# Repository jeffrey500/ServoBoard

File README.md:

# ServoBoard V2.1

## Introduction
This project contains a 2 layer PCB that has the designed purpose of driving up to 4 PWM servo motors of variable input voltage, with the entire board itself being powered by a variable voltage.  
This board is controlled by an atmega328PB and has 6n137 optocouplers.

## Microcontroller
The microcontroller (MCU) on this board is the atmega328PB which can be programmed via the USB-C connection on the side of the board through the use of a CH340C USB-to-UART serial converter IC.  
The atmega328PB was chosen as it is a simple and stable MCU that can be programmed using the Arduino IDE, and is an upgrade over the atmega328.
The MCU utilizes an external 16 MHz crystal oscillator. 

Note: the USB connection can only be used after initial bootloader burning (see ISP section).

## Power
There are 3 different voltages present on the board: input, servo, and 5V. 

Using the LM2596S buck voltage regulator, the board can utilize a maximum of 3A at the output of the Buck regulator. 
The efficiency of the LM2596S 92%. The board accepts a voltage range of 40V and can step it down to 1.25V-35V.
You can adjust the output voltage of the LM2596S by adjusting the screw on the blue potentiometer.
The potentiometer acts as a voltage divider which alters the internal PWM duty cycle. 

The use of an AMS1117-5.0 fixed 5V low dropout linear voltage regulator further steps down the voltage from the servo voltage to 5V to power the MCU.
The dropout range is 1.3V with a max input voltage of 15V.

Note: you should be careful when adjusting output of the LM2596S when using voltages higher than 15V as you can potentially destroy the AMS1117 LDO.
Additionally, the servo voltage should be high enough such that the MCU after the LDO has sufficient a sufficient voltage.

## Servo PWM pins
Servo motors can be driven using one or many of the 4 sets of SIGNAL-POWER-GROUND male header pins. 
The connected servo motors are driven by the voltage output of the LM2596S Buck Converter. 
A large 2200uF capacitor is placed very close to the servo pin headers to provide power during momentary high current draw. 

## Optocouplers
The Board contains 3 6n137 high-speed digital Optocouplers, mounted on DIP-8 sockets, allowing for interfacing with optical isolation.
The 6n137 mounted on the U5 DIP-8 socket is oriented as an input for digital signals while U4 and U6 are oriented as outputs.

## Board Design
This Board utilizes a 2 layer stackup. The top layer is signal with a ground pour.
The bottom layer is a ground plane of which effort was put in to ensure as much continuity as possible. 
The top and bottom ground layers are connected via stitching.
A power plane and cut is placed around the servo pin headers so that surges of power are drawn from the nearby capacitor.
Extra thermal vias are placed around the ground pin of the LM2596S.

## In-System Programming (ISP)
Following the assembly of the board you will need to do burn the bootloader of the board to be able to use the USB-C port to program the atmega328PB. 
To do this, it is recommended to use any Arduino in addition to its ability to be an [ISP flasher](https://docs.arduino.cc/built-in-examples/arduino-isp/ArduinoISP/).

### Schematic

### Board Without Pours

### Top Copper

### Bottom Copper

## Application
The design application of this board is within a CNC White board plotter //add link for which this board controls a pen plotter that is controlled by an Ardunio CNC Shield, interfacing through an optocoupler.
The board input voltage is 12V, with the servo needing 7V.

## BOM
The cost of each board at low production quantities is around $15 CAD.

## LICENSE
[ServoBoard](https://github.com/jeffrey500/ServoBoard) © 2026 by [Jeffrey Zhu](https://jzhu.ca) is licensed under [CC BY-NC 4.0](https://creativecommons.org/licenses/by-nc/4.0/)

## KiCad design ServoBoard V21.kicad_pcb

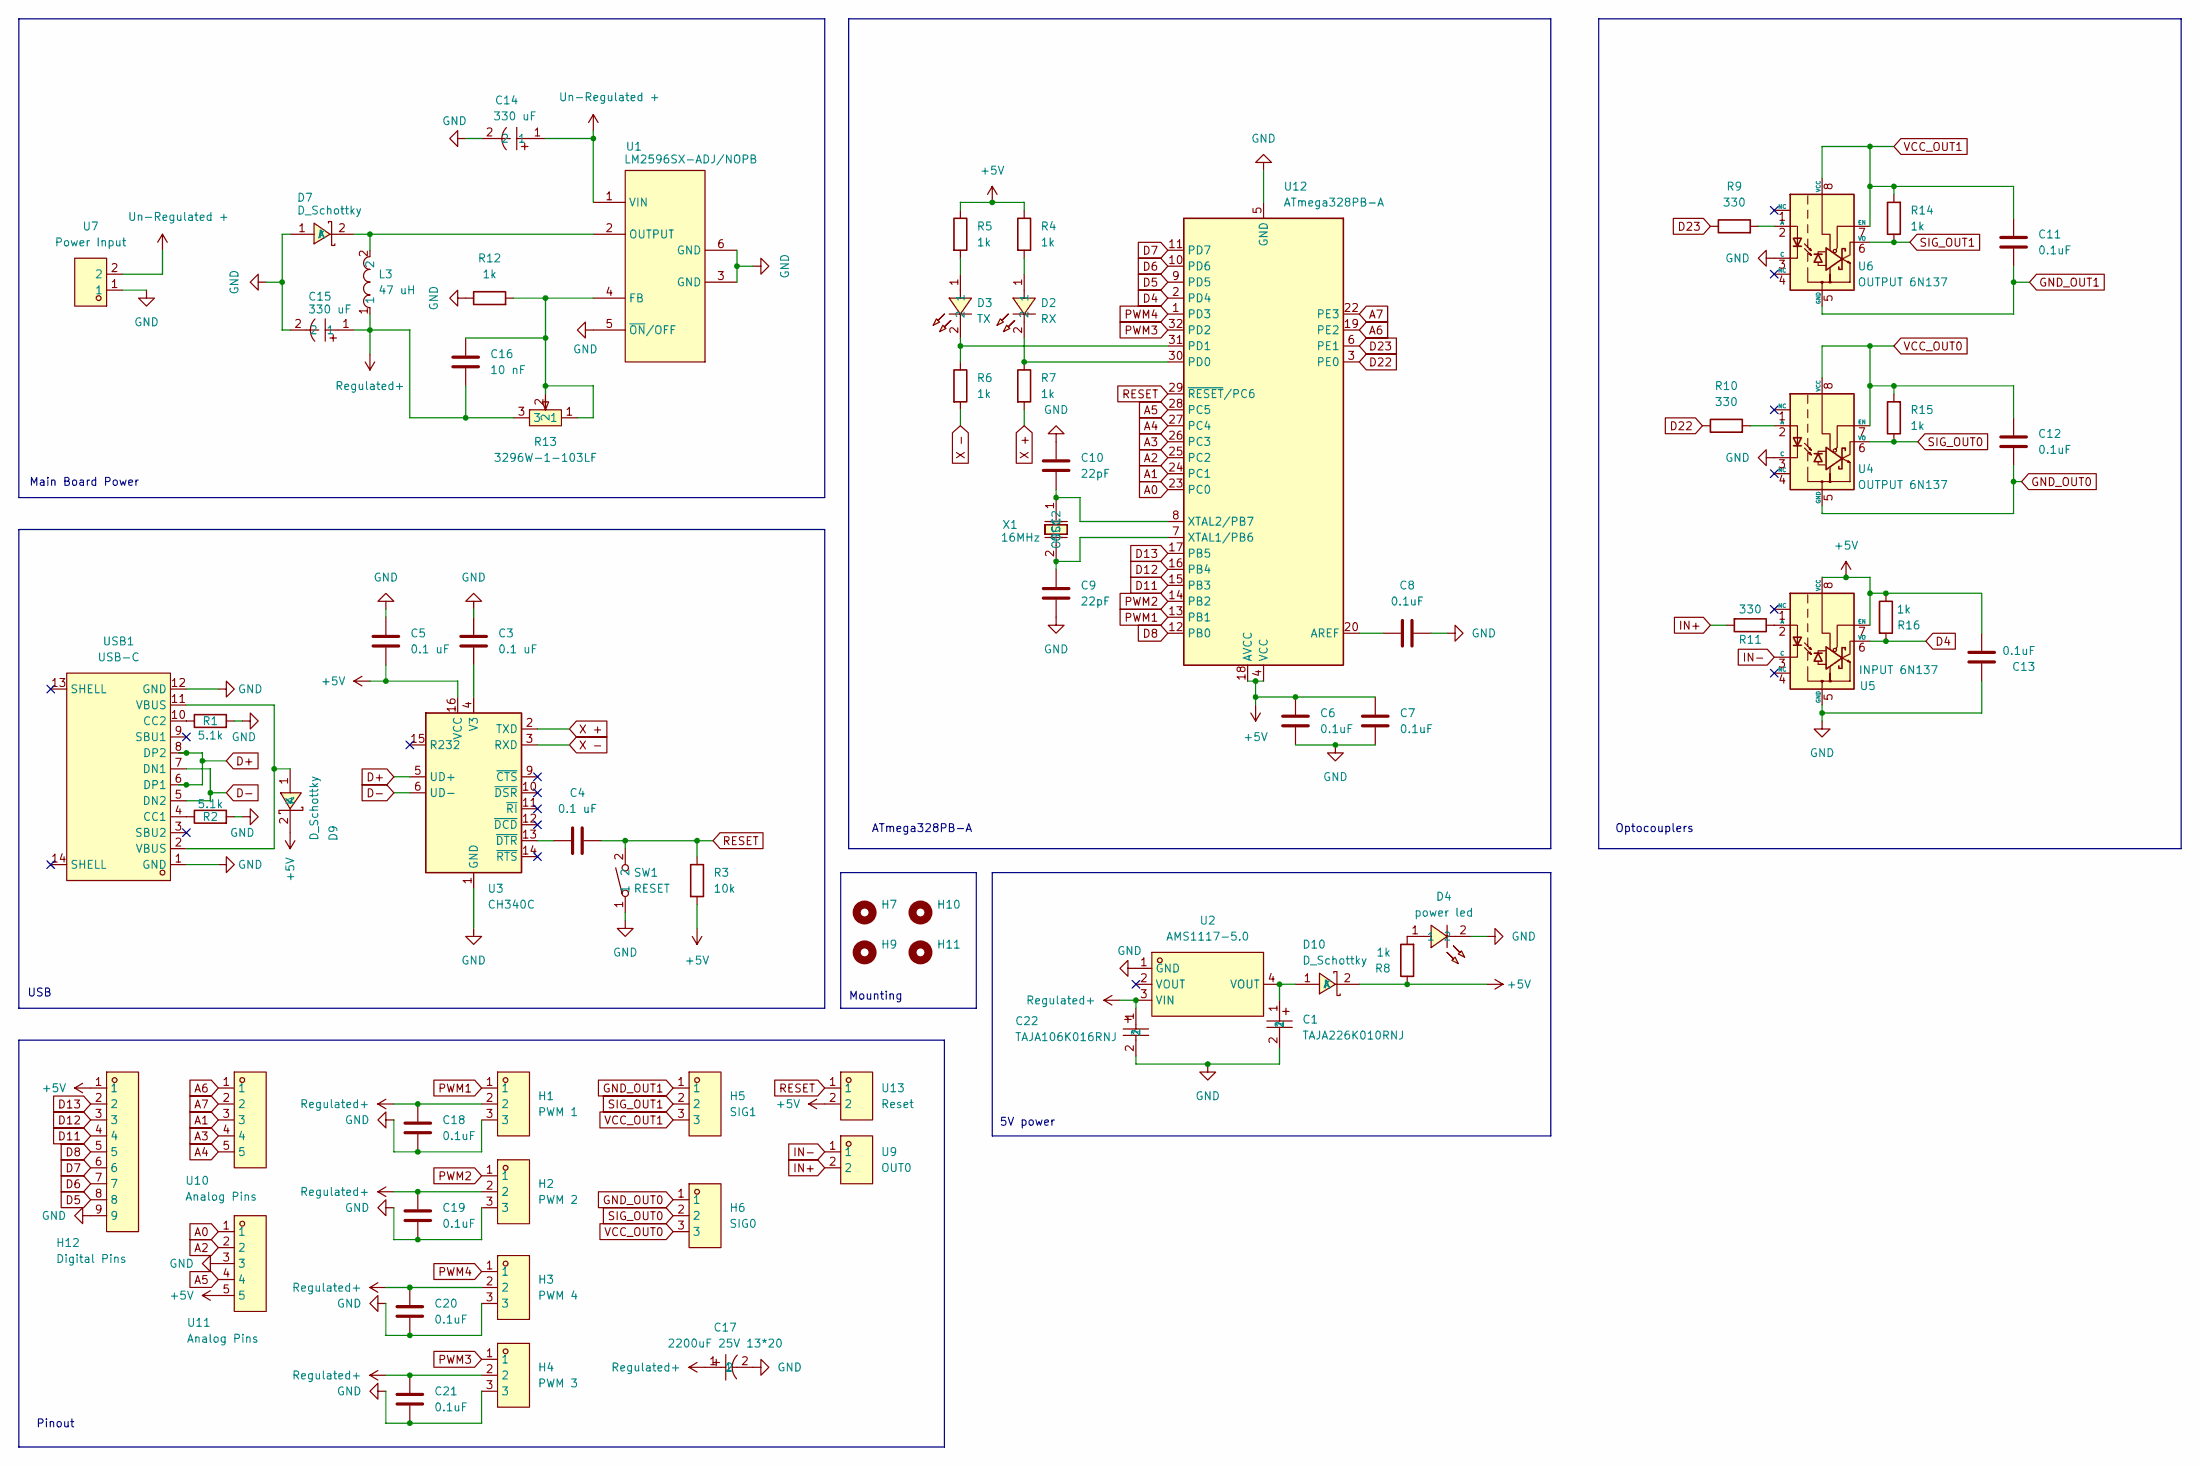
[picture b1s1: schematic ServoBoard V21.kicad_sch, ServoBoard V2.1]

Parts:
C1: TAJA226K010RNJ; CASE-A_3216; MPN TAJA226K010RNJ; LCSC Part C11366
C3, C4, C5: 0.1 uF; C_0805_2012Metric
C6, C7, C8, C11, C12, C13, C18, C19, C20, C21: 0.1uF; C_0805_2012Metric
C9, C10: 22pF; C_0805_2012Metric
C14, C15: 330 uF; CAP-TH_BD12.5-P5.00-D0.6-FD; LCSC Part C2835679
C16: 10 nF; C_0805_2012Metric
C17: 2200uF 25V 13*20; CAP-TH_BD13.0-P5.00-D1.2-FD; MPN KM228M025J20RR0VH2FP0; LCSC Part C44598
C22: TAJA106K016RNJ; CAP-SMD_L3.2-W1.6-RD-C7171; MPN TAJA106K016RNJ; LCSC Part C7171
D2: RX; LED1206-FD; LCSC Part C28310439
D3: TX; LED1206-FD; LCSC Part C28310439
D4: power led; LED1206-FD; LCSC Part C28310439
D7, D9, D10: D_Schottky; SMA_L4.4-W2.8-LS5.4-R-RD; LCSC Part C22452
H1: PWM 1; CONN-TH_HX-PZ2.54-1X3P-ZZ; LCSC Part C32713269
H2: PWM 2; CONN-TH_HX-PZ2.54-1X3P-ZZ; LCSC Part C32713269
H3: PWM 4; CONN-TH_HX-PZ2.54-1X3P-ZZ; LCSC Part C32713269
H4: PWM 3; CONN-TH_HX-PZ2.54-1X3P-ZZ; LCSC Part C32713269
H5: SIG1; CONN-TH_HX-PZ2.54-1X3P-ZZ; LCSC Part C32713269
H6: SIG0; CONN-TH_HX-PZ2.54-1X3P-ZZ; LCSC Part C32713269
H7, H9, H10, H11: MountingHole; MountingHole_4.3mm_M4
H12: Digital Pins; HDR-TH_9P-P2.54-V-F-3; LCSC Part C42372501
L3: 47 uH; IND-SMD_L12.3-W12.3; LCSC Part C962356
R1, R2: 5.1k; R_0805_2012Metric
R3: 10k; R_0805_2012Metric
R4, R5, R6, R7, R8, R12, R14, R15, R16: 1k; R_0805_2012Metric
R9, R10, R11: 330; R_0805_2012Metric
R13: 3296W-1-103LF; RES-ADJ-TH_3296W; MPN 3296W-1-103LF; LCSC Part C34846
SW1: RESET; SW-SMD_L4.0-W2.9-LS5.0; LCSC Part C557591
U1: LM2596SX-ADJ/NOPB; TO-263-5_L10.2-W8.9-P1.70-TL; MPN LM2596SX-ADJ/NOPB; LCSC Part C29781
U2: AMS1117-5.0; SOT-223_L6.5-W3.5-P2.30-LS7.0-BR; MPN AMS1117-5.0; LCSC Part C6187
U3: CH340C; SOIC-16_3.9x9.9mm_P1.27mm
U4, U6: OUTPUT 6N137; DIP-8_W7.62mm_Socket
U5: INPUT 6N137; DIP-8_W7.62mm_Socket
U7: Power Input; CONN-TH_P5.00_KF301-5.0-2P; LCSC Part C474881
U9: OUT0; HDR-TH_2P-P2.54-V-M-3; LCSC Part C32713268
U10, U11: Analog Pins; HDR-TH_5P-P2.54-V-M; LCSC Part C32713271
U12: ATmega328PB-A; TQFP-32_7x7mm_P0.8mm
U13: Reset; HDR-TH_2P-P2.54-V-M-3; LCSC Part C32713268
USB1: USB-C; USB-C-SMD_TYPE-C-6PIN-2MD-073; LCSC Part C2765186
X1: 16MHz; OSC-TH_L10.0-W4.5-P5.00; LCSC Part C443538

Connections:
+5V: C5.2, C6.1, C7.1, C13.1, D9.2 (K), D10.2 (K), H12.1, R3.2, R4.1, R5.1, R8.1, R16.1, U3.16 (VCC), U5.7 (EN), U5.8 (VCC), U11.5, U12.4 (VCC), U12.18 (AVCC), U13.2
A0: U11.1, U12.23 (PC0)
A1: U10.3, U12.24 (PC1)
A2: U11.2, U12.25 (PC2)
A3: U10.4, U12.26 (PC3)
A4: U10.5, U12.27 (PC4)
A5: U11.4, U12.28 (PC5)
A6: U10.1, U12.19 (PE2)
A7: U10.2, U12.22 (PE3)
D4: R16.2, U5.6 (VO), U12.2 (PD4)
D5: H12.8, U12.9 (PD5)
D6: H12.7, U12.10 (PD6)
D7: H12.6, U12.11 (PD7)
D8: H12.5, U12.12 (PB0)
D11: H12.4, U12.15 (PB3)
D12: H12.3, U12.16 (PB4)
D13: H12.2, U12.17 (PB5)
D22: R10.1, U12.3 (PE0)
D23: R9.1, U12.6 (PE1)
D+: U3.5 (UD+), USB1.6 (DP1), USB1.8 (DP2)
D-: U3.6 (UD-), USB1.5 (DN2), USB1.7 (DN1)
GND: C1.2, C3.1, C5.1, C6.2, C7.2, C8.2, C9.2, C10.1, C13.2, C14.2, C15.2, C17.2, C18.2, C19.2, C20.2, C21.2, C22.2, D4.2, D7.1 (A), H1.3, H2.3, H3.3, H4.3, H12.9, R1.2, R2.2, R12.1, SW1.1, U1.3 (GND), U1.5 (~ON/OFF), U1.6 (GND), U2.1 (GND), U3.1 (GND), U4.3 (C), U5.5 (GND), U6.3 (C), U7.1, U11.3, U12.5 (GND), U12.21 (GND), USB1.1 (GND), USB1.12 (GND)
GND_OUT0: C12.1, H6.1, U4.5 (GND)
GND_OUT1: C11.1, H5.1, U6.5 (GND)
IN+: R11.2, U9.2
IN-: U5.3 (C), U9.1
unnamed: D2.1, R4.2
unnamed: D3.1, R5.2
unnamed: D4.1, R8.2
unnamed: D7.2 (K), L3.2, U1.2 (OUTPUT)
unnamed: D9.1 (A), USB1.2 (VBUS), USB1.11 (VBUS)
unnamed: C1.1, D10.1 (A), U2.4 (VOUT)
unnamed: C16.1, R12.2, R13.1, R13.2, U1.4 (FB)
unnamed: C3.2, U3.4 (V3)
unnamed: C4.1, U3.13 (~DTR)
unnamed: R10.2, U4.2 (A)
unnamed: R11.1, U5.2 (A)
unnamed: R9.2, U6.2 (A)
unnamed: C8.1, U12.20 (AREF)
unnamed: D2.2, R7.1, U12.30 (PD0)
unnamed: D3.2, R6.1, U12.31 (PD1)
unnamed: C9.1, U12.7 (XTAL1/PB6), X1.2 (OSC2)
unnamed: C10.2, U12.8 (XTAL2/PB7), X1.1 (OSC1)
unnamed: R2.1, USB1.4 (CC1)
unnamed: R1.1, USB1.10 (CC2)
PWM1: H1.1, U12.13 (PB1)
PWM2: H2.1, U12.14 (PB2)
PWM3: H4.1, U12.32 (PD2)
PWM4: H3.1, U12.1 (PD3)
RESET: C4.2, R3.1, SW1.2, U12.29 (~RESET/PC6), U13.1
Regulated+: C15.1, C16.2, C17.1, C18.1, C19.1, C20.1, C21.1, C22.1, H1.2, H2.2, H3.2, H4.2, L3.1, R13.3, U2.3 (VIN)
SIG_OUT0: H6.2, R15.1, U4.6 (VO)
SIG_OUT1: H5.2, R14.1, U6.6 (VO)
Un-Regulated +: C14.1, U1.1 (VIN), U7.2
VCC_OUT0: C12.2, H6.3, R15.2, U4.7 (EN), U4.8 (VCC)
VCC_OUT1: C11.2, H5.3, R14.2, U6.7 (EN), U6.8 (VCC)
X +: R7.2, U3.2 (TXD)
X -: R6.2, U3.3 (RXD)

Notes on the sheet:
USB
ATmega328PB-A
5V power
Optocouplers
Pinout
Main Board Power
Mounting

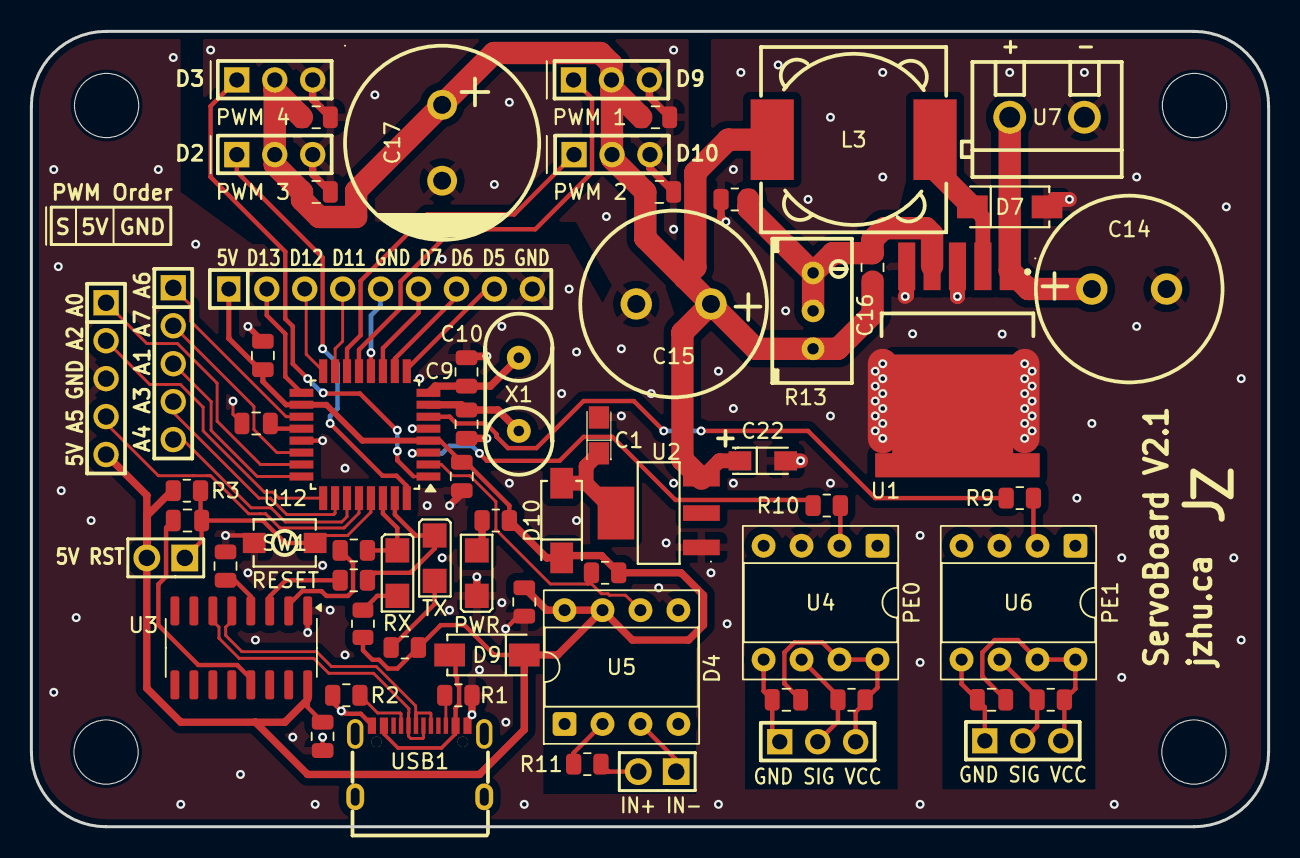
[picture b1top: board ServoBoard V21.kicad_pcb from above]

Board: 2 copper layers, 82.8 x 53.2 mm, 70 parts (0 on the bottom side), 58 nets.

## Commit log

2026-06-28 Add .gitignore file
2026-06-28 Added final IRL PCB picture
2026-06-28 Update README with new details
2026-06-28 added IRL ServoBoard_pic.jpg
